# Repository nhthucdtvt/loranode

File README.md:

# geolocation_lorawannode
project geolocation
using lorawan node 868Mhz
mcu: efm32
module: lora 868Mhz sx1276

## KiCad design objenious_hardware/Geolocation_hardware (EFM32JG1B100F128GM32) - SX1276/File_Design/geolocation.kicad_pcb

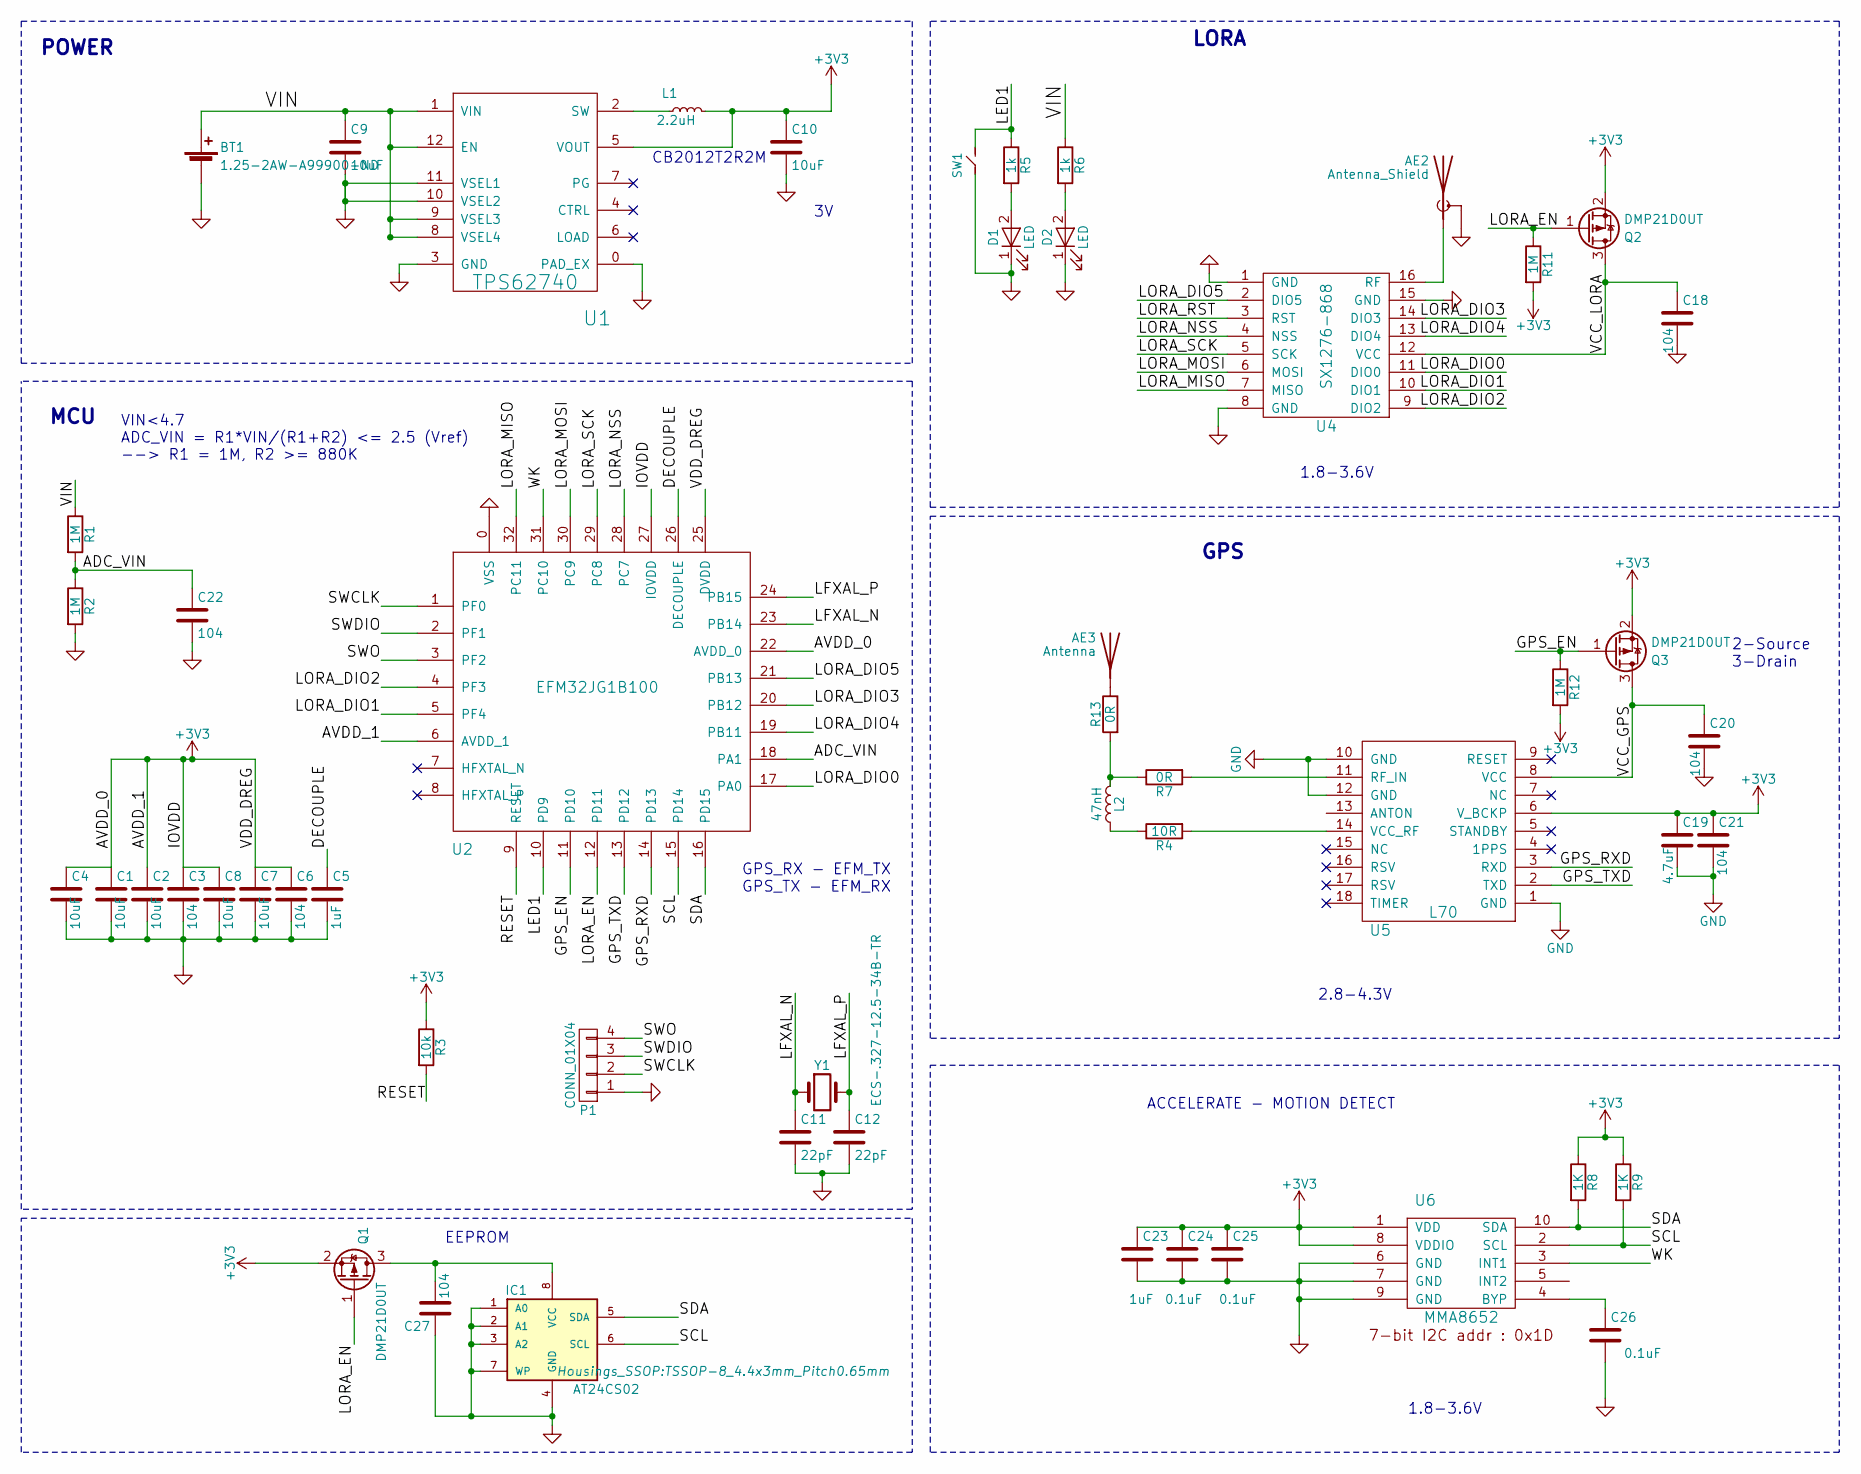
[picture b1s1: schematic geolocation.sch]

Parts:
AE2: Antenna_Shield; IPEX_Connector
AE3: Antenna; IPEX_Connector
BT1: 1.25-2AW-A99900-ND; Hirose_DF13-02P-1.25DS_02x1.25mm_Angled
C1, C2, C4, C7, C8, C9, C10: 10uF; C_0402
C3, C6, C18, C20, C21, C22, C27: 104; C_0402
C5, C23: 1uF; C_0402
C11, C12: 22pF; C_0402
C19: 4.7uF; C_0402
C24, C25, C26: 0.1uF; C_0402
D1, D2: LED; LED_0603
IC1: AT24CS02; TSSOP-8_4.4x3mm_Pitch0.65mm
L1: 2.2uH; R_0805
L2: 47nH; C_0402
P1: CONN_01X04; Pin_Header_Straight_1x04
Q1, Q2, Q3: DMP21D0UT; SOT-523
R1, R2, R11, R12: 1M; R_0402
R3: 10k; R_0402
R4: 10R; R_0402
R5, R6: 1k; R_0402
R7, R13: 0R; R_0402
R8, R9: 1K; R_0402
SW1: SW_2P; SW
U1: TPS62740; WSON-12_3x2
U2: EFM32JG1B100; QFN-32-1EP_5x5mm_Pitch0.5mm
U4: SX1276-868; SX1278-433-RA2
U5: L70; L70_GPS
U6: MMA8652; DFN-10_2x2mm_Pitch0.4mm
Y1: ECS-.327-12.5-34B-TR; Crystal_SMD_32768

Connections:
+3V3: C1.1, C2.1, C3.1, C4.1, C6.1, C7.1, C8.1, C10.1, C19.1, C21.1, C23.1, C24.1, C25.1, L1.2, Q1.2 (S), Q2.2 (S), Q3.2 (S), R3.1, R8.1, R9.1, R11.2, R12.2, U1.5 (VOUT), U2.6 (AVDD_1), U2.22 (AVDD_0), U2.25 (DVDD), U2.27 (IOVDD), U5.6 (V_BCKP), U6.1 (VDD), U6.8 (VDDIO)
/ADC_VIN: C22.1, R1.2, R2.1, U2.18 (PA1)
/DECOUPLE: C5.1, U2.26 (DECOUPLE)
/GPS_EN: Q3.1 (G), R12.1, U2.11 (PD10)
/GPS_RXD: U2.14 (PD13), U5.3 (RXD)
/GPS_TXD: U2.13 (PD12), U5.2 (TXD)
/LED1: R5.1, SW1.2, U2.10 (PD9)
/LFXAL_N: C11.1, U2.23 (PB14), Y1.1
/LFXAL_P: C12.1, U2.24 (PB15), Y1.2
/LORA_DIO0: U2.17 (PA0), U4.11 (DIO0)
/LORA_DIO1: U2.5 (PF4), U4.10 (DIO1)
/LORA_DIO2: U2.4 (PF3), U4.9 (DIO2)
/LORA_DIO3: U2.20 (PB12), U4.14 (DIO3)
/LORA_DIO4: U2.19 (PB11), U4.13 (DIO4)
/LORA_DIO5: U2.21 (PB13), U4.2 (DIO5)
/LORA_EN: Q1.1 (G), Q2.1 (G), R11.1, U2.12 (PD11)
/LORA_MISO: U2.32 (PC11), U4.7 (MISO)
/LORA_MOSI: U2.30 (PC9), U4.6 (MOSI)
/LORA_NSS: U2.28 (PC7), U4.4 (NSS)
/LORA_RST: U4.3 (RST)
/LORA_SCK: U2.29 (PC8), U4.5 (SCK)
/RESET: R3.2, U2.9 (RESET)
/SCL: IC1.6 (SCL), R9.2, U2.15 (PD14), U6.2 (SCL)
/SDA: IC1.5 (SDA), R8.2, U2.16 (PD15), U6.10 (SDA)
/SWCLK: P1.2, U2.1 (PF0)
/SWDIO: P1.3, U2.2 (PF1)
/SWO: P1.4, U2.3 (PF2)
/VCC_GPS: C20.1, Q3.3 (D), U5.8 (VCC)
/VCC_LORA: C18.1, Q2.3 (D), U4.12 (VCC)
/VIN: BT1.1 (+), C9.1, R1.1, R6.1, U1.1 (VIN), U1.8 (VSEL4), U1.9 (VSEL3), U1.12 (EN)
/WK: U2.31 (PC10), U6.3 (INT1)
GND: AE2.2 (Shield), BT1.2 (-), C1.2, C2.2, C3.2, C4.2, C5.2, C6.2, C7.2, C8.2, C9.2, C10.2, C11.2, C12.2, C18.2, C19.2, C20.2, C21.2, C22.2, C23.2, C24.2, C25.2, C26.2, C27.1, D1.1 (K), D2.1 (K), IC1.1 (A0), IC1.2 (A1), IC1.3 (A2), IC1.4 (GND), IC1.7 (WP), P1.1, R2.2, SW1.1, U1.0 (PAD_EX), U1.3 (GND), U1.10 (VSEL2), U1.11 (VSEL1), U2.0 (VSS), U4.1 (GND), U4.8 (GND), U4.15 (GND), U5.1 (GND), U5.10 (GND), U5.12 (GND), U6.6 (GND), U6.7 (GND), U6.9 (GND)
unnamed: AE2.1 (A), U4.16 (RF)
unnamed: AE3.1, R13.1
unnamed: C26.1, U6.4 (BYP)
unnamed: C27.2, IC1.8 (VCC), Q1.3 (D)
unnamed: D1.2 (A), R5.2
unnamed: D2.2 (A), R6.2
unnamed: L1.1, U1.2 (SW)
unnamed: L2.1, R4.1
unnamed: L2.2, R7.1, R13.2
unnamed: R4.2, U5.14 (VCC_RF)
unnamed: R7.2, U5.11 (RF_IN)

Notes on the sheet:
GPS
LORA
MCU
POWER
1.8-3.6V
2.8-4.3V
CB2012T2R2M
ACCELERATE - MOTION DETECT
2-Source 3-Drain
EEPROM
VIN<4.7 ADC_VIN = R1*VIN/(R1+R2) <= 2.5 (Vref) --> R1 = 1M, R2 >= 880K
GPS_RX - EFM_TX GPS_TX - EFM_RX

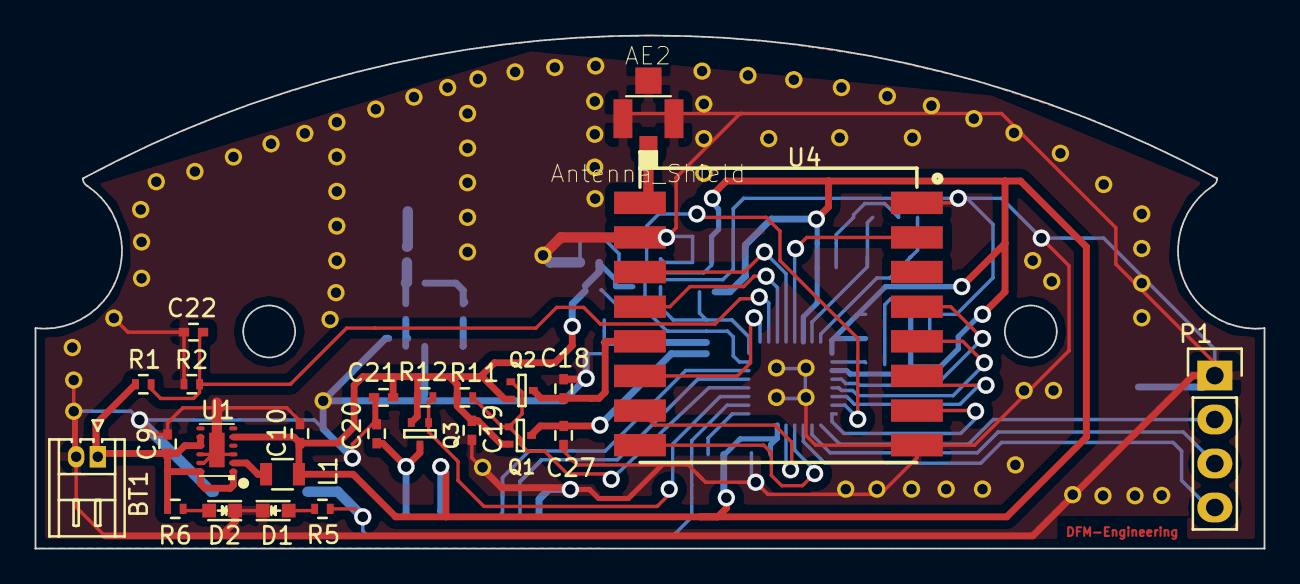
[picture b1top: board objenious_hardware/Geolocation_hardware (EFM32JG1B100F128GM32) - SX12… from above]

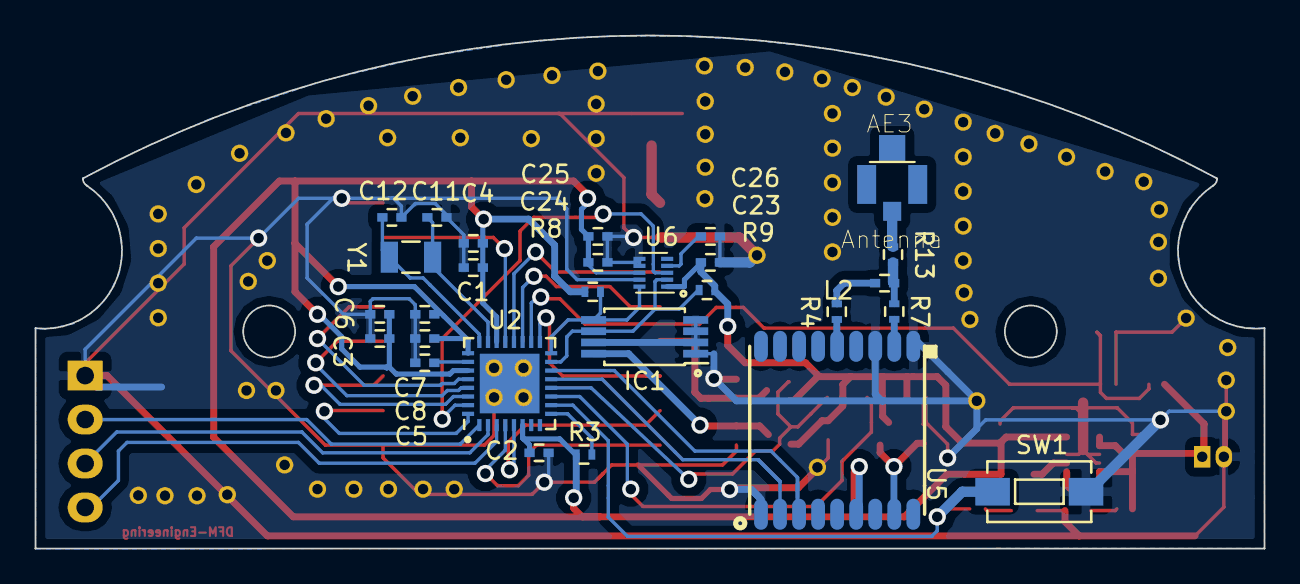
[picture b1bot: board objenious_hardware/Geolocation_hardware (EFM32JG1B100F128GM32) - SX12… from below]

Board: 2 copper layers, 71.0 x 29.6 mm, 53 parts (28 on the bottom side), 42 nets.

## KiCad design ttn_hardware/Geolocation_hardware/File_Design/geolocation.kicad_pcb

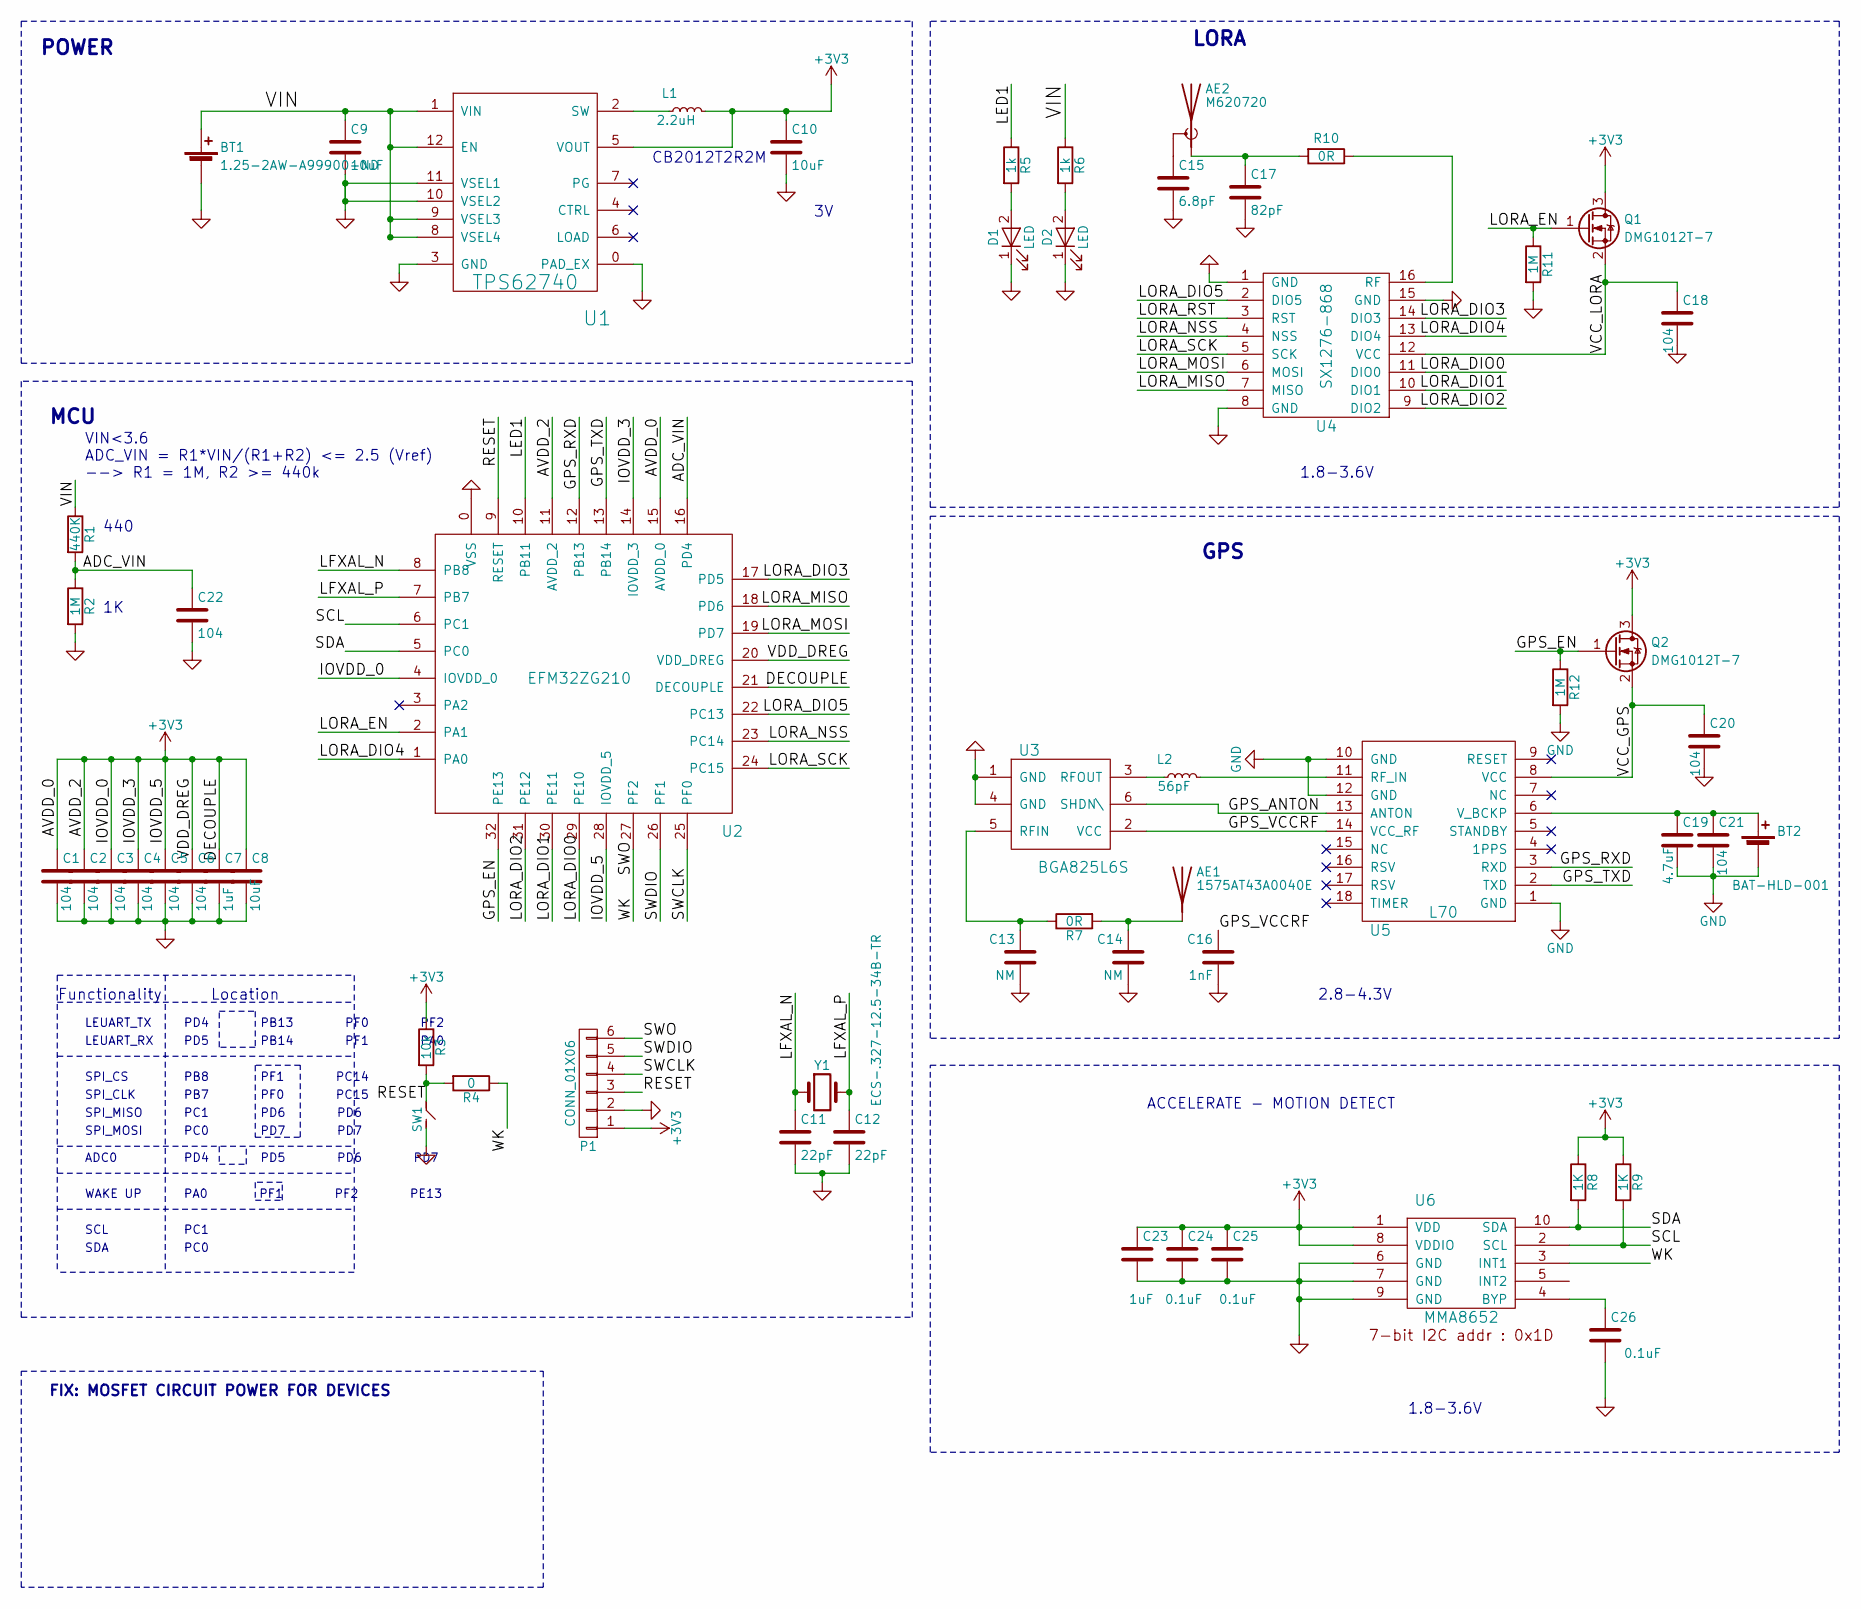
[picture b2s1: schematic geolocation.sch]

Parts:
AE1: 1575AT43A0040E; 1575AT43A0040E-ANTENNA
AE2: M620720; M620720-ANTENNA
BT1: 1.25-2AW-A99900-ND; Hirose_DF13-02P-1.25DS_02x1.25mm_Angled
BT2: BAT-HLD-001
C1, C2, C3, C4, C5, C6, C18, C20, C21, C22: 104; C_0603
C7, C23: 1uF; C_0603
C8, C9, C10: 10uF; C_0603
C11, C12: 22pF; C_0603
C13, C14: NM; C_0603
C15: 6.8pF; C_0603
C16: 1nF; C_0603
C17: 82pF; C_0603
C19: 4.7uF; C_0603
C24, C25, C26: 0.1uF; C_0603
D1, D2: LED; LED_0603
L1: 2.2uH; R_0805
L2: 56pF; R_0603
P1: CONN_01X06; Pin_Header_Straight_1x06
Q1, Q2: DMG1012T-7; SOT-523
R1: 440K; R_0603
R2, R11, R12: 1M; R_0603
R3: 10k; R_0603
R4: 0; R_0603
R5, R6: 1k; R_0603
R7, R10: 0R; R_0603
R8, R9: 1K; R_0603
SW1: SW_2P; SW
U1: TPS62740; WSON-12_3x2
U2: EFM32ZG210; QFN-32-1EP_6x6mm_Pitch0.65mm
U3: BGA825L6S; TSLP-6-3
U4: SX1276-868; RL-SX1276-868
U5: L70; L70_GPS
U6: MMA8652; DFN-10_2x2mm_Pitch0.4mm
Y1: ECS-.327-12.5-34B-TR; Crystal_SMD_32768

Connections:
+3V3: C1.1, C2.1, C3.1, C4.1, C5.1, C6.1, C7.1, C8.1, C10.1, C23.1, C24.1, C25.1, L1.2, P1.1, Q1.3 (D), Q2.3 (D), R3.1, R8.1, R9.1, U1.5 (VOUT), U2.4 (IOVDD_0), U2.11 (AVDD_2), U2.14 (IOVDD_3), U2.15 (AVDD_0), U2.20 (VDD_DREG), U2.21 (DECOUPLE), U2.28 (IOVDD_5), U6.1 (VDD), U6.8 (VDDIO)
/ADC_VIN: C22.1, R1.2, R2.1, U2.16 (PD4)
/GPS_ANTON: U3.6 (SHDN\), U5.13 (ANTON)
/GPS_EN: Q2.1 (G), R12.1, U2.32 (PE13)
/GPS_RXD: U2.12 (PB13), U5.3 (RXD)
/GPS_TXD: U2.13 (PB14), U5.2 (TXD)
/GPS_VCCRF: C16.1, U3.2 (VCC), U5.14 (VCC_RF)
/LED1: R5.1, U2.10 (PB11)
/LFXAL_N: C11.1, U2.8 (PB8), Y1.1
/LFXAL_P: C12.1, U2.7 (PB7), Y1.2
/LORA_DIO0: U2.29 (PE10), U4.11 (DIO0)
/LORA_DIO1: U2.30 (PE11), U4.10 (DIO1)
/LORA_DIO2: U2.31 (PE12), U4.9 (DIO2)
/LORA_DIO3: U2.17 (PD5), U4.14 (DIO3)
/LORA_DIO4: U2.1 (PA0), U4.13 (DIO4)
/LORA_DIO5: U2.22 (PC13), U4.2 (DIO5)
/LORA_EN: Q1.1 (G), R11.1, U2.2 (PA1)
/LORA_MISO: U2.18 (PD6), U4.7 (MISO)
/LORA_MOSI: U2.19 (PD7), U4.6 (MOSI)
/LORA_NSS: U2.23 (PC14), U4.4 (NSS)
/LORA_RST: U4.3 (RST)
/LORA_SCK: U2.24 (PC15), U4.5 (SCK)
/RESET: P1.3, R3.2, R4.2, SW1.1, U2.9 (RESET)
/SCL: R9.2, U2.6 (PC1), U6.2 (SCL)
/SDA: R8.2, U2.5 (PC0), U6.10 (SDA)
/SWCLK: P1.4, U2.25 (PF0)
/SWDIO: P1.5, U2.26 (PF1)
/SWO: P1.6, R4.1, U2.27 (PF2), U6.3 (INT1)
/VCC_GPS: C20.1, Q2.2 (S), U5.8 (VCC)
/VCC_LORA: C18.1, Q1.2 (S), U4.12 (VCC)
/VIN: BT1.1 (+), C9.1, R1.1, R6.1, U1.1 (VIN), U1.8 (VSEL4), U1.9 (VSEL3), U1.12 (EN)
GND: BT1.2 (-), BT2.2 (-), C1.2, C2.2, C3.2, C4.2, C5.2, C6.2, C7.2, C8.2, C9.2, C10.2, C11.2, C12.2, C13.2, C14.2, C15.2, C16.2, C17.2, C18.2, C19.2, C20.2, C21.2, C22.2, C23.2, C24.2, C25.2, C26.2, D1.1 (K), D2.1 (K), P1.2, R2.2, R11.2, R12.2, SW1.2, U1.0 (PAD_EX), U1.3 (GND), U1.10 (VSEL2), U1.11 (VSEL1), U2.0 (VSS), U3.1 (GND), U3.4 (GND), U4.1 (GND), U4.8 (GND), U4.15 (GND), U5.1 (GND), U5.10 (GND), U5.12 (GND), U6.6 (GND), U6.7 (GND), U6.9 (GND)
unnamed: AE1.1, C14.1, R7.2
unnamed: AE2.1 (A), C17.1, R10.2
unnamed: AE2.2 (Shield), C15.1
unnamed: BT2.1 (+), C19.1, C21.1, U5.6 (V_BCKP)
unnamed: C13.1, R7.1, U3.5 (RFIN)
unnamed: C26.1, U6.4 (BYP)
unnamed: D1.2 (A), R5.2
unnamed: D2.2 (A), R6.2
unnamed: L1.1, U1.2 (SW)
unnamed: L2.1, U3.3 (RFOUT)
unnamed: L2.2, U5.11 (RF_IN)
unnamed: R10.1, U4.16 (RF)

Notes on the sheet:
Functionality
Location
LEUART_TX
LEUART_RX
PD4 PB13 PF0 PF2
PD5 PB14 PF1 PA0
SPI_CS
SPI_CLK
SPI_MISO
SPI_MOSI
PB8 PF1 PC14
PB7 PF0 PC15
PC1 PD6 PD6
PC0 PD7 PD7
ADC0
PD4 PD5 PD6 PD7
WAKE UP
PA0 PF1 PF2 PE13
GPS
LORA
MCU
POWER
VIN<3.6 ADC_VIN = R1*VIN/(R1+R2) <= 2.5 (Vref) --> R1 = 1M, R2 >= 440k
1.8-3.6V
2.8-4.3V
CB2012T2R2M
440
SCL
SDA
PC0
PC1
ACCELERATE - MOTION DETECT
FIX: MOSFET CIRCUIT POWER FOR DEVICES

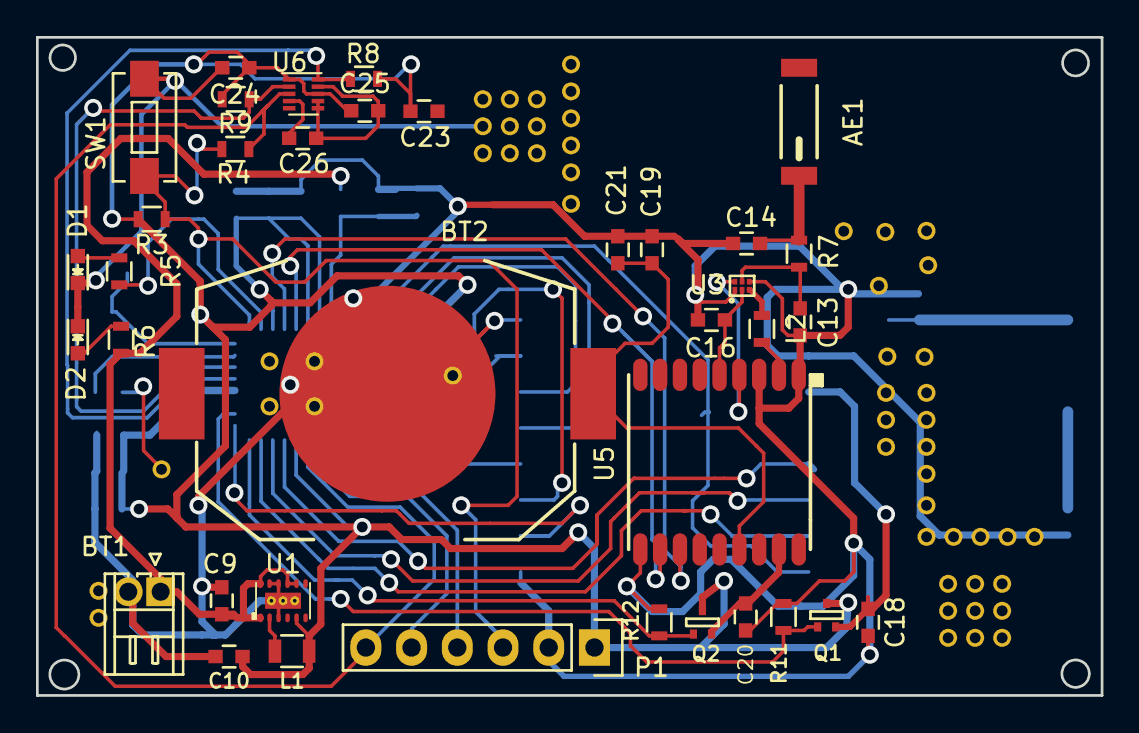
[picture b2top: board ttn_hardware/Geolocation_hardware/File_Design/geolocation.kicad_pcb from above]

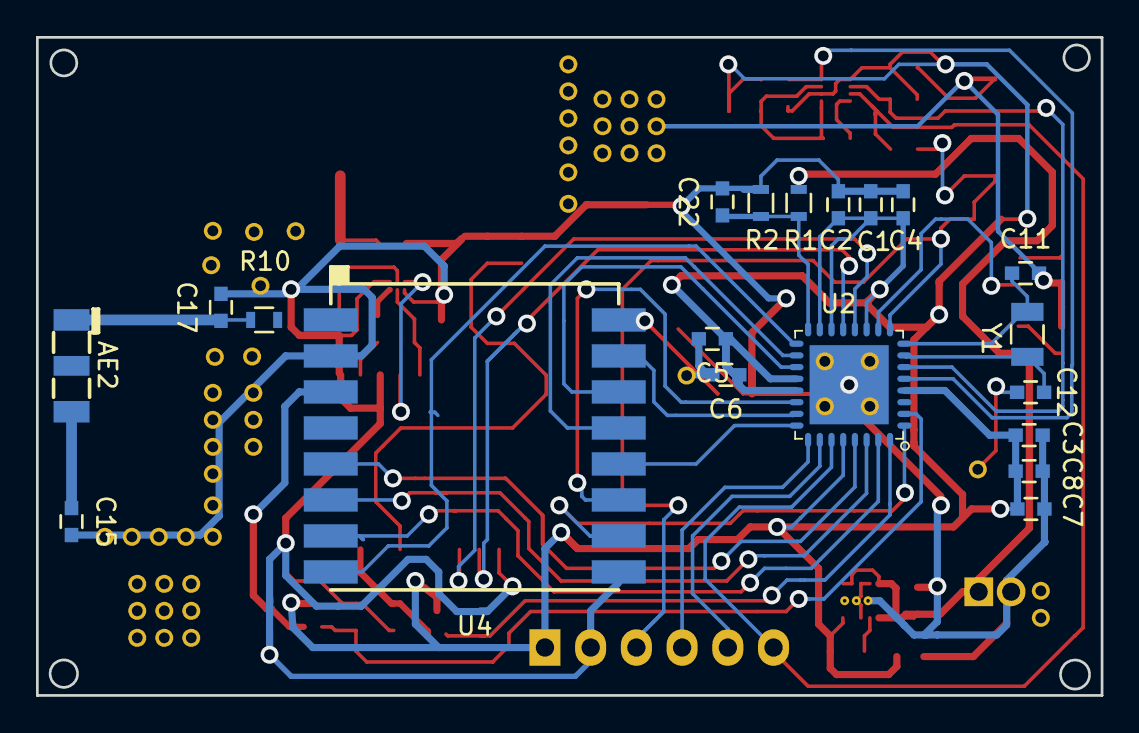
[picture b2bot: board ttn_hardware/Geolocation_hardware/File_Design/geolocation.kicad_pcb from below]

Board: 2 copper layers, 59.2 x 36.6 mm, 57 parts (20 on the bottom side), 42 nets.

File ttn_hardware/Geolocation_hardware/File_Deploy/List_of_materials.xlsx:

title | GEOLOCATION
date | 2017-09-05
rev | 0
company | DFM-ENGINEERING
reference | value | footprint
AE1 | 1575AT43A0040E | my_lib:1575AT43A0040E-ANTENNA | https://www.digikey.com/product-detail/en/johanson-technolog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
AE2 | M620720 | my_lib:M620720-ANTENNA | https://www.digikey.com/product-detail/en/ethertronics-inc/M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
BT1 | 1.25-2AW | Connectors_Hirose:Hirose_DF13-02P-1.25DS_02x1.25mm_Angled | https://www.digikey.com/product-detail/en/te-connectivity-am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
BT2 | BAT-HLD-001 | my_lib:BAT-HLD-001 | https://www.digikey.com/product-detail/en/linx-technologies-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
C1 | 0.1uF | Capacitors_SMD:C_0603
C10 | 10uF | Capacitors_SMD:C_0603
C11 | 22pF | Capacitors_SMD:C_0603
C12 | 22pF | Capacitors_SMD:C_0603
C13 | NM | Capacitors_SMD:C_0603
C14 | NM | Capacitors_SMD:C_0603
C15 | 6.8pF | Capacitors_SMD:C_0603
C16 | 1nF | Capacitors_SMD:C_0603
C17 | 82pF | Capacitors_SMD:C_0603
C18 | 0.1uF | Capacitors_SMD:C_0603
C19 | 4.7uF | Capacitors_SMD:C_0603
C2 | 0.1uF | Capacitors_SMD:C_0603
C20 | 0.1uF | Capacitors_SMD:C_0603
C21 | 0.1uF | Capacitors_SMD:C_0603
C22 | 0.1uF | Capacitors_SMD:C_0603
C23 | 1uF | Capacitors_SMD:C_0603
C24 | 0.1uF | Capacitors_SMD:C_0603
C25 | 0.1uF | Capacitors_SMD:C_0603
C26 | 0.1uF | Capacitors_SMD:C_0603
C3 | 0.1uF | Capacitors_SMD:C_0603
C4 | 0.1uF | Capacitors_SMD:C_0603
C5 | 0.1uF | Capacitors_SMD:C_0603
C6 | 0.1uF | Capacitors_SMD:C_0603
C7 | 1uF | Capacitors_SMD:C_0603
C8 | 10uF | Capacitors_SMD:C_0603
C9 | 10uF | Capacitors_SMD:C_0603
D1 | LED | LEDs:LED_0603
D2 | LED | LEDs:LED_0603
L1 | 2.2uH | Resistors_SMD:R_0805
L2 | 56pF | Resistors_SMD:R_0603
P1 | CONN_01X06 | Pin_Headers:Pin_Header_Straight_1x06
Q1 | DMG1012T-7 | my_lib:SOT-523 | https://www.digikey.com/product-detail/en/diodes-incorporate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
Q2 | DMG1012T-7 | my_lib:SOT-523
R1 | 440K | Resistors_SMD:R_0603
R10 | 0R | Resistors_SMD:R_0603
R11 | 1M | Resistors_SMD:R_0603
R12 | 1M | Resistors_SMD:R_0603
R2 | 1M | Resistors_SMD:R_0603
R3 | 10k | Resistors_SMD:R_0603
R5 | 1k | Resistors_SMD:R_0603
R6 | 1k | Resistors_SMD:R_0603
R7 | 0R | Resistors_SMD:R_0603
R8 | 1K | Resistors_SMD:R_0603
R9 | 1K | Resistors_SMD:R_0603
SW1 | SW_2P | my_lib:SW | http://tme.vn/Search.aspx?keyword=SW603625-W2
U1 | TPS62740 | my_lib:WSON-12_3x2 | https://www.digikey.com/product-detail/en/texas-instruments/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
U2 | EFM32ZG210 | my_lib:QFN-32-1EP_6x6mm_Pitch0.65mm | https://www.digikey.com/product-detail/en/silicon-labs/EFM32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
U3 | BGA825L6S | my_lib:TSLP-6-3 | https://www.digikey.com/product-detail/en/infineon-technolog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
U4 | SX1276-868 | my_lib:RL-SX1276-868 | alibaba
U5 | L70 | my_lib:L70_GPS | https://www.alibaba.com/product-detail/-Electronic-Component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
U6 | MMA8652 | Footprint_lib:DFN-10_2x2mm_Pitch0.4mm | https://www.digikey.com/product-detail/en/nxp-usa-inc/MMA865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
Y1 | ECS-.327-12.5-34B-TR | my_lib:Crystal_SMD_32768 | https://www.digikey.com/product-detail/en/ecs-inc/ECS-.327-1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
 | 56pF |  | https://www.digikey.com/product-detail/en/samsung-electro-me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
 | 1nF |  | https://www.digikey.com/product-detail/en/kemet/C0402C102K5R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
 | 6.8pF |  | https://www.digikey.com/product-detail/en/yageo/CC0402BRNPO9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
 | 82pF |  | https://www.digikey.com/product-detail/en/samsung-electro-me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
 | 18pF |  | https://www.digikey.com/product-detail/en/murata-electronics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
 | 22pF |  | https://www.digikey.com/product-detail/en/murata-electronics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
 | 0.1uF |  | https://www.digikey.com/product-detail/en/murata-electronics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
 | 1uF |  | https://www.digikey.com/product-detail/en/samsung-electro-me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
 | 10uF |  | https://www.digikey.com/product-detail/en/murata-electronics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
 | 4.7uF |  | https://www.digikey.com/product-detail/en/murata-electronics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
 | 1K |  | https://www.digikey.com/product-detail/en/yageo/RC0402JR-071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
 | 10K |  | https://www.digikey.com/product-detail/en/yageo/RC0402JR-071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
 | 440K |  | https://www.digikey.com/product-detail/en/yageo/RC0402FR-074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
 | 1M |  | https://www.digikey.com/product-detail/en/yageo/RC0402FR-071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
 | LED |  | https://www.digikey.com/product-detail/en/sunled/XZMDK68W-2/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
 | 2.2uH |  | https://www.digikey.com/product-detail/en/taiyo-yuden/CB2012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

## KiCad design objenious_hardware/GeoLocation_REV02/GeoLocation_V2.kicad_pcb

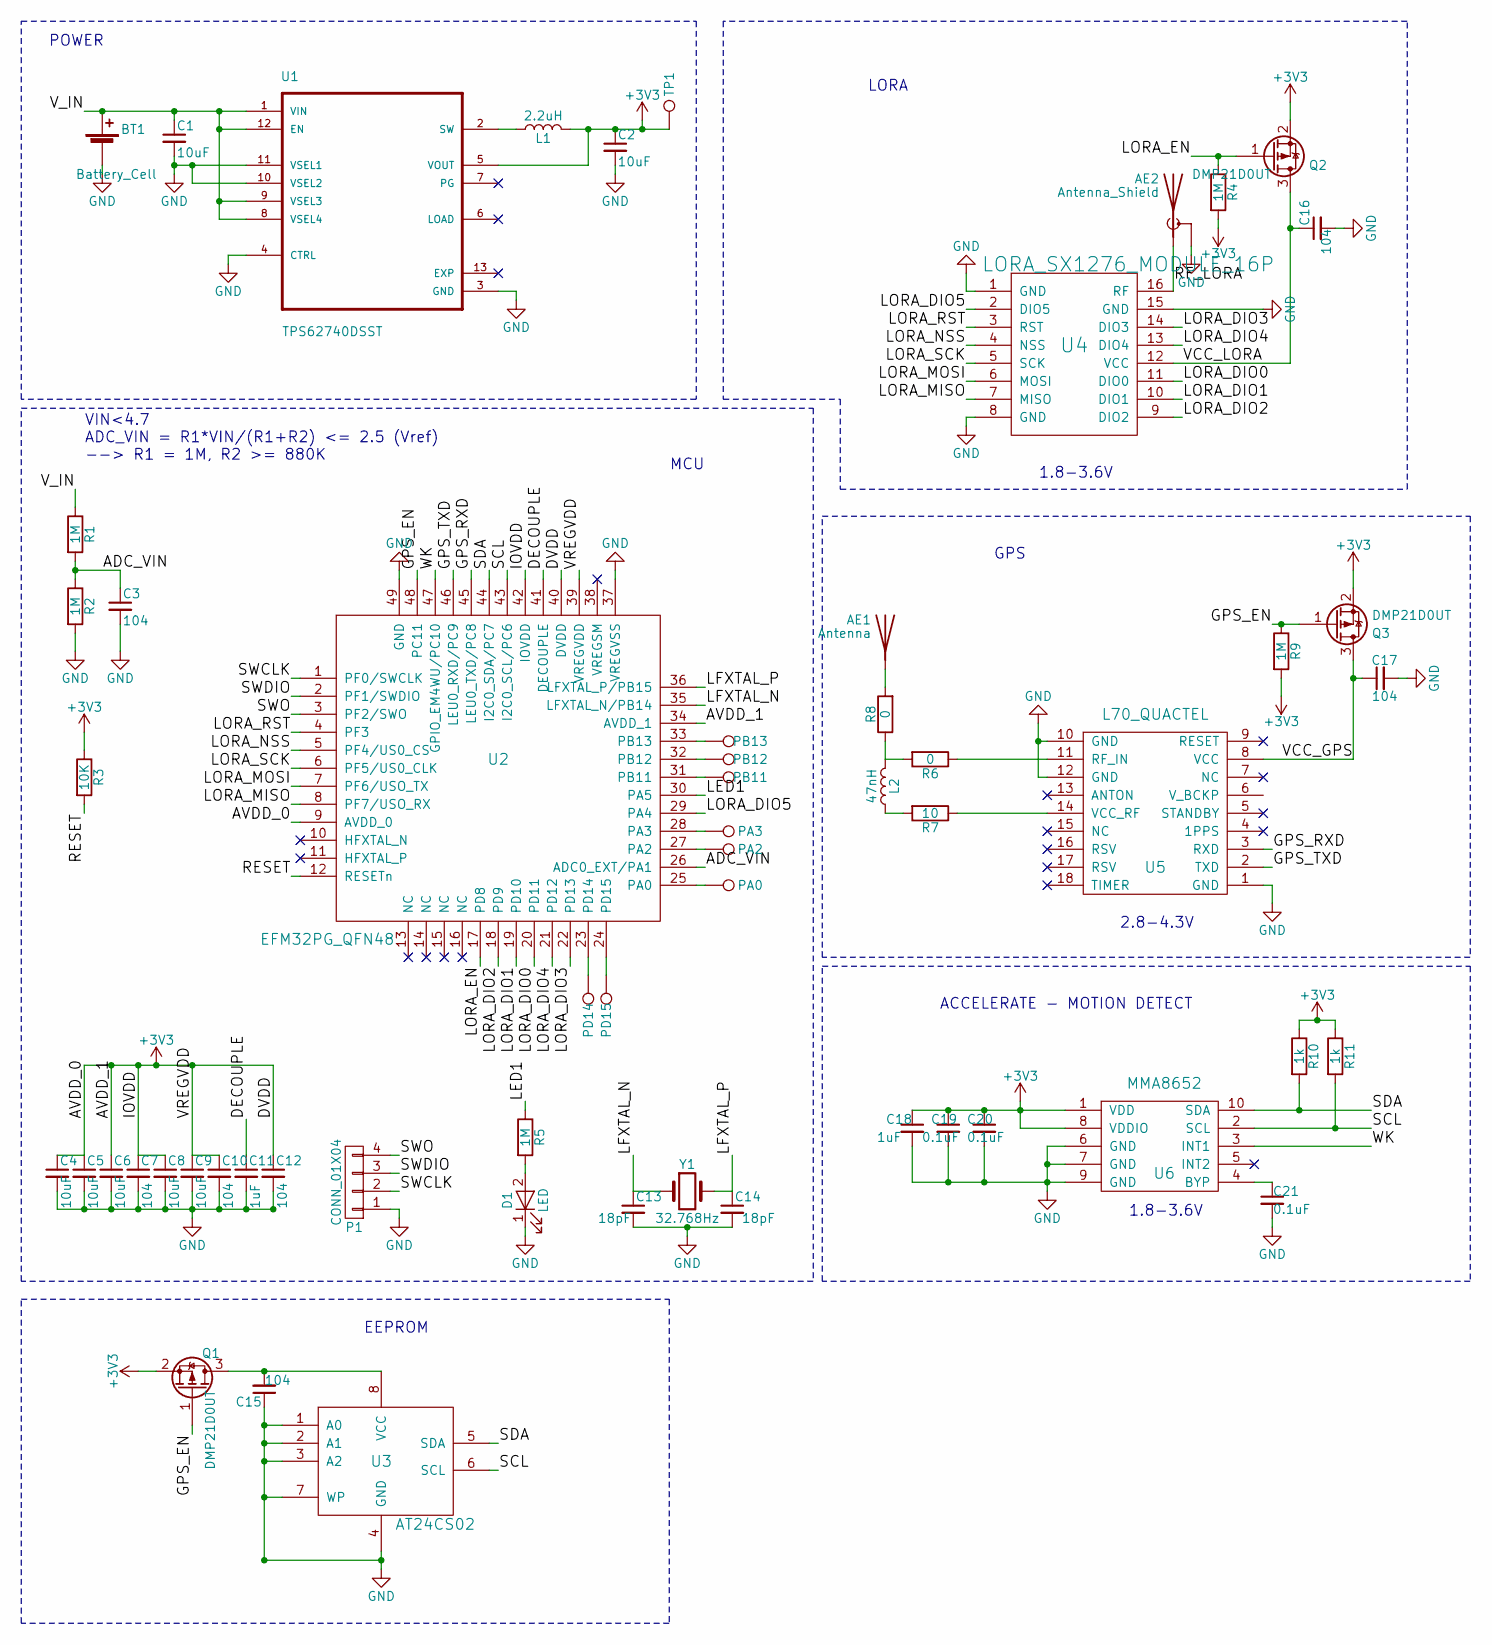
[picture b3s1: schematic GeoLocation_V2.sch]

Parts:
AE1: Antenna; IPEX_Connector
AE2: Antenna_Shield; IPEX_Connector
BT1: Battery_Cell; Hirose_DF13-02P-1.25DS_02x1.25mm_Angled
C1, C2, C4, C5, C6, C8, C9: 10uF; C_0402
C3, C7, C10, C12, C15, C16, C17: 104; C_0402
C11, C18: 1uF; C_0402
C13, C14: 18pF; C_0402
C19, C20, C21: 0.1uF; C_0402
D1: LED; LED_0603
L1: 2.2uH; R_0805
L2: 47nH; C_0402
P1: CONN_01X04; Pin_Header_Straight_1x04
PA0, PA2, PA3: TEST_1P; TestPoint
PB11, PB12, PB13: TEST_1P; TestPoint
PD14, PD15: TEST_1P; TestPoint
Q1, Q2, Q3: DMP21D0UT; SOT-523
R1, R2, R4, R5, R9: 1M; R_0402
R3: 10K; R_0402
R6, R8: 0; R_0402
R7: 10; R_0402
R10, R11: 1k; R_0402
TP1: TEST_1P; TestPoint
U1: TPS62740DSST; WSON-12_3x2
U2: EFM32PG_QFN48; QFN-48-1EP_7x7mm_Pitch0.5mm
U3: AT24CS02; TSSOP-8_4.4x3mm_Pitch0.65mm
U4: LORA_SX1276_MODULE_16P; SX1278-433-RA2
U5: L70_QUACTEL; L70_GPS
U6: MMA8652; DFN-10_2x2mm_Pitch0.4mm
Y1: 32.768Hz; Crystal_SMD_32768

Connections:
+3V3: C2.1, C4.1, C5.1, C6.1, C7.1, C8.1, C9.1, C10.1, C12.1, C18.1, C19.1, C20.1, L1.2, Q1.2 (S), Q2.2 (S), Q3.2 (S), R3.1, R4.2, R9.2, R10.1, R11.1, TP1.1, U1.5 (VOUT), U2.9 (AVDD_0), U2.34 (AVDD_1), U2.39 (VREGVDD), U2.40 (DVDD), U2.42 (IOVDD), U6.1 (VDD), U6.8 (VDDIO)
/ADC_VIN: C3.1, R1.2, R2.1, U2.26 (ADC0_EXT/PA1)
/DECOUPLE: C11.1, U2.41 (DECOUPLE)
/GPS_EN: Q1.1 (G), Q3.1 (G), R9.1, U2.48 (PC11)
/GPS_RXD: U2.45 (LEU0_TXD/PC8), U5.3 (RXD)
/GPS_TXD: U2.46 (LEU0_RXD/PC9), U5.2 (TXD)
/LED1: R5.1, U2.30 (PA5)
/LFXTAL_N: C13.1, U2.35 (LFXTAL_N/PB14), Y1.1
/LFXTAL_P: C14.1, U2.36 (LFXTAL_P/PB15), Y1.2
/LORA_DIO0: U2.20 (PD11), U4.11 (DIO0)
/LORA_DIO1: U2.19 (PD10), U4.10 (DIO1)
/LORA_DIO2: U2.18 (PD9), U4.9 (DIO2)
/LORA_DIO3: U2.22 (PD13), U4.14 (DIO3)
/LORA_DIO4: U2.21 (PD12), U4.13 (DIO4)
/LORA_DIO5: U2.29 (PA4), U4.2 (DIO5)
/LORA_EN: Q2.1 (G), R4.1, U2.17 (PD8)
/LORA_MISO: U2.8 (PF7/USO_RX), U4.7 (MISO)
/LORA_MOSI: U2.7 (PF6/USO_TX), U4.6 (MOSI)
/LORA_NSS: U2.5 (PF4/US0_CS), U4.4 (NSS)
/LORA_RST: U2.4 (PF3), U4.3 (RST)
/LORA_SCK: U2.6 (PF5/US0_CLK), U4.5 (SCK)
/RESET: R3.2, U2.12 (RESETn)
/RF_LORA: AE2.1 (A), U4.16 (RF)
/SCL: R11.2, U2.43 (I2C0_SCL/PC6), U3.6 (SCL), U6.2 (SCL)
/SDA: R10.2, U2.44 (I2C0_SDA/PC7), U3.5 (SDA), U6.10 (SDA)
/SWCLK: P1.2, U2.1 (PF0/SWCLK)
/SWDIO: P1.3, U2.2 (PF1/SWDIO)
/SWO: P1.4, U2.3 (PF2/SWO)
/VCC_GPS: C17.1, Q3.3 (D), U5.8 (VCC)
/VCC_LORA: C16.1, Q2.3 (D), U4.12 (VCC)
/V_IN: BT1.1 (+), C1.1, R1.1, U1.1 (VIN), U1.8 (VSEL4), U1.9 (VSEL3), U1.12 (EN)
/WK: U2.47 (GPIO_EM4WU/PC10), U6.3 (INT1)
GND: AE2.2 (Shield), BT1.2 (-), C1.2, C2.2, C3.2, C4.2, C5.2, C6.2, C7.2, C8.2, C9.2, C10.2, C11.2, C12.2, C13.2, C14.2, C15.1, C16.2, C17.2, C18.2, C19.2, C20.2, C21.2, D1.1 (K), P1.1, R2.2, U1.0, U1.3 (GND), U1.4 (CTRL), U1.10 (VSEL2), U1.11 (VSEL1), U2.37 (VREGVSS), U2.49 (GND), U3.1 (A0), U3.2 (A1), U3.3 (A2), U3.4 (GND), U3.7 (WP), U4.1 (GND), U4.8 (GND), U4.15 (GND), U5.1 (GND), U5.10 (GND), U5.12 (GND), U6.6 (GND), U6.7 (GND), U6.9 (GND)
unnamed: AE1.1, R8.2
unnamed: C15.2, Q1.3 (D), U3.8 (VCC)
unnamed: C21.1, U6.4 (BYP)
unnamed: D1.2 (A), R5.2
unnamed: L1.1, U1.2 (SW)
unnamed: L2.1, R7.2
unnamed: L2.2, R6.2, R8.1
unnamed: PA0.1, U2.25 (PA0)
unnamed: PA2.1, U2.27 (PA2)
unnamed: PA3.1, U2.28 (PA3)
unnamed: PB11.1, U2.31 (PB11)
unnamed: PB12.1, U2.32 (PB12)
unnamed: PB13.1, U2.33 (PB13)
unnamed: PD14.1, U2.23 (PD14)
unnamed: PD15.1, U2.24 (PD15)
unnamed: R6.1, U5.11 (RF_IN)
unnamed: R7.1, U5.14 (VCC_RF)

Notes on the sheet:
VIN<4.7 ADC_VIN = R1*VIN/(R1+R2) <= 2.5 (Vref) --> R1 = 1M, R2 >= 880K
1.8-3.6V
2.8-4.3V
ACCELERATE - MOTION DETECT
GPS
LORA
MCU
POWER
EEPROM

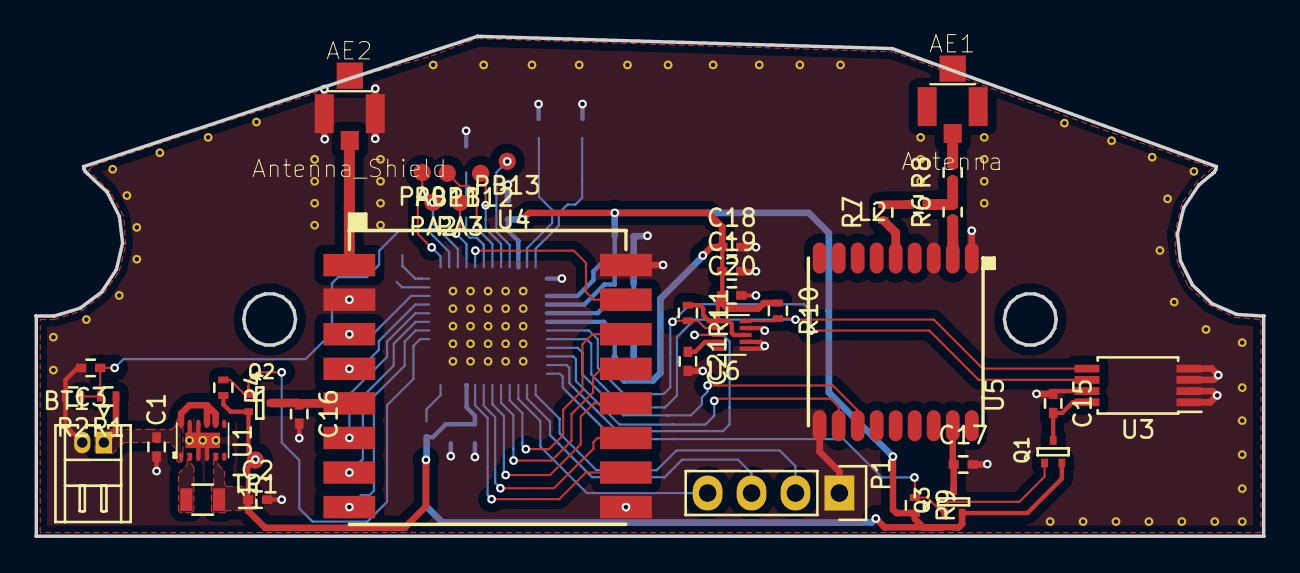
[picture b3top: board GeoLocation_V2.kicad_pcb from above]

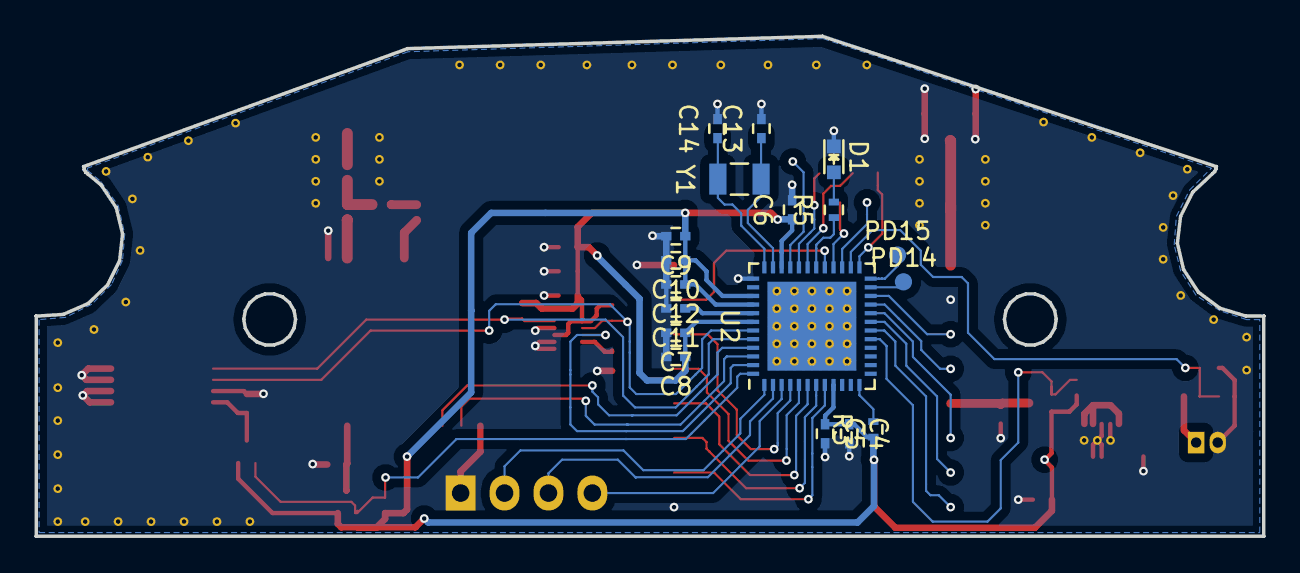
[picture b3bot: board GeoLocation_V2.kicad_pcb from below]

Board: 2 copper layers, 71.1 x 29.0 mm, 58 parts (18 on the bottom side), 50 nets.

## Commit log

2018-11-21 add files
2018-11-21 add test loriot
